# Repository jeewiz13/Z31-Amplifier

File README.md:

# Z31-Amplifier
New Amplifier that fits into stock Z31 Amplifier Housing
This isn't for the faint of heart.  This requires desoldering skills as the original header and DIN socket are reused.
It could use a few tweaks with spacing of the amplifier chips. They are off a little left or right. The footprints could also use a few tweaks as well. Works as is though. 
I originally thought the amplifier chips wouldn't fit inbetween the original metal mounting clamps.  They do but I was going to make an adapter out of aluminum to have it sink to the case. This spacing is rather large.  This spacing should be resolved if another version were to be made.

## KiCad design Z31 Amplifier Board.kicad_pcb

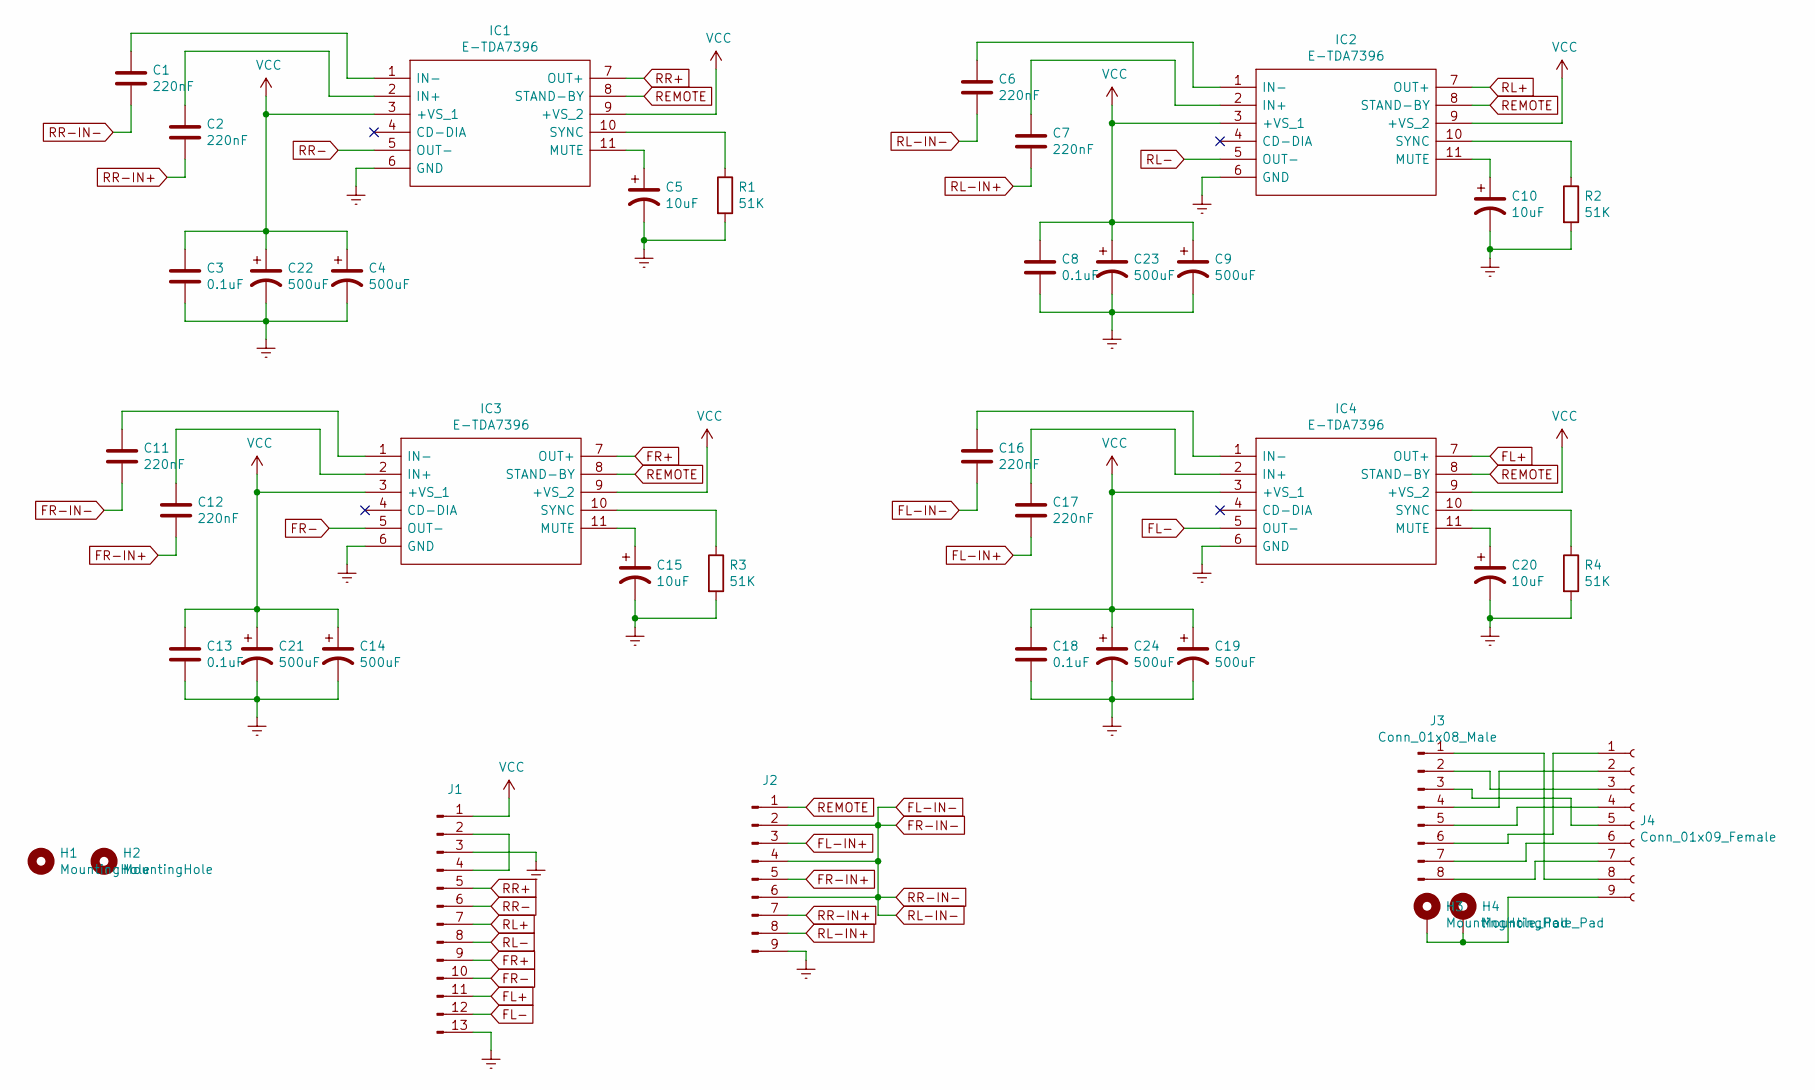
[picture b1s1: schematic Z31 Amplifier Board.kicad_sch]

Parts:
C1, C2, C6, C7, C11, C12, C16, C17: 220nF; C_Rect_L7.2mm_W2.5mm_P5.00mm_FKS2_FKP2_MKS2_MKP2
C3, C8, C13, C18: 0.1uF; C_Disc_D3.8mm_W2.6mm_P2.50mm
C4, C9, C14, C19, C21, C22, C23, C24: 500uF; CP_Radial_D10.0mm_P5.00mm
C5, C10, C15, C20: 10uF; CP_Radial_D5.0mm_P2.00mm
H1, H2: MountingHole; MountingHole_4.3mm_M4_ISO14580_Pad_TopBottom
H3, H4: MountingHole_Pad; MountingHole_2.5mm_Pad
IC1, IC2, IC3, IC4: E-TDA7396; TO170P500X1960X2210-11P; Mouser Part Number 511-E-TDA7396
J1: Conn_01x13_Male; Z31 Big Connector
J2: Conn_01x09_Male; Z31 Input Connector
J3: Conn_01x08_Male; 300ZX DIN Board Edge Connector
J4: Conn_01x09_Female; Din-8 Socket
R1, R2, R3, R4: 51K; R_Axial_DIN0309_L9.0mm_D3.2mm_P15.24mm_Horizontal

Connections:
Earth: C3.2, C4.2, C5.2, C8.2, C9.2, C10.2, C13.2, C14.2, C15.2, C18.2, C19.2, C20.2, C21.2, C22.2, C23.2, C24.2, IC1.6 (GND), IC2.6 (GND), IC3.6 (GND), IC4.6 (GND), J1.3, J1.13, J2.9, R1.2, R2.2, R3.2, R4.2
FL+: IC4.7 (OUT+), J1.11
FL-: IC4.5 (OUT-), J1.12
FL-IN+: C17.2, J2.3
FL-IN-: C1.2, C6.2, C11.2, C16.2, J2.2, J2.4, J2.6
FR+: IC3.7 (OUT+), J1.9
FR-: IC3.5 (OUT-), J1.10
FR-IN+: C12.2, J2.5
unnamed: C1.1, IC1.1 (IN-)
unnamed: C2.1, IC1.2 (IN+)
unnamed: C5.1, IC1.11 (MUTE)
unnamed: C6.1, IC2.1 (IN-)
unnamed: C7.1, IC2.2 (IN+)
unnamed: C10.1, IC2.11 (MUTE)
unnamed: C11.1, IC3.1 (IN-)
unnamed: C12.1, IC3.2 (IN+)
unnamed: C15.1, IC3.11 (MUTE)
unnamed: C16.1, IC4.1 (IN-)
unnamed: C17.1, IC4.2 (IN+)
unnamed: C20.1, IC4.11 (MUTE)
unnamed: H3.1, H4.1, J4.9
unnamed: IC1.10 (SYNC), R1.1
unnamed: IC2.10 (SYNC), R2.1
unnamed: IC3.10 (SYNC), R3.1
unnamed: IC4.10 (SYNC), R4.1
unnamed: J1.2, J1.4
unnamed: J3.1, J4.8
unnamed: J3.2, J4.3
unnamed: J3.3, J4.5
unnamed: J3.4, J4.2
unnamed: J3.5, J4.4
unnamed: J3.6, J4.1
unnamed: J3.7, J4.6
unnamed: J3.8, J4.7
REMOTE: IC1.8 (STAND-BY), IC2.8 (STAND-BY), IC3.8 (STAND-BY), IC4.8 (STAND-BY), J2.1
RL+: IC2.7 (OUT+), J1.7
RL-: IC2.5 (OUT-), J1.8
RL-IN+: C7.2, J2.8
RR+: IC1.7 (OUT+), J1.5
RR-: IC1.5 (OUT-), J1.6
RR-IN+: C2.2, J2.7
VCC: C3.1, C4.1, C8.1, C9.1, C13.1, C14.1, C18.1, C19.1, C21.1, C22.1, C23.1, C24.1, IC1.3 (+VS_1), IC1.9 (+VS_2), IC2.3 (+VS_1), IC2.9 (+VS_2), IC3.3 (+VS_1), IC3.9 (+VS_2), IC4.3 (+VS_1), IC4.9 (+VS_2), J1.1

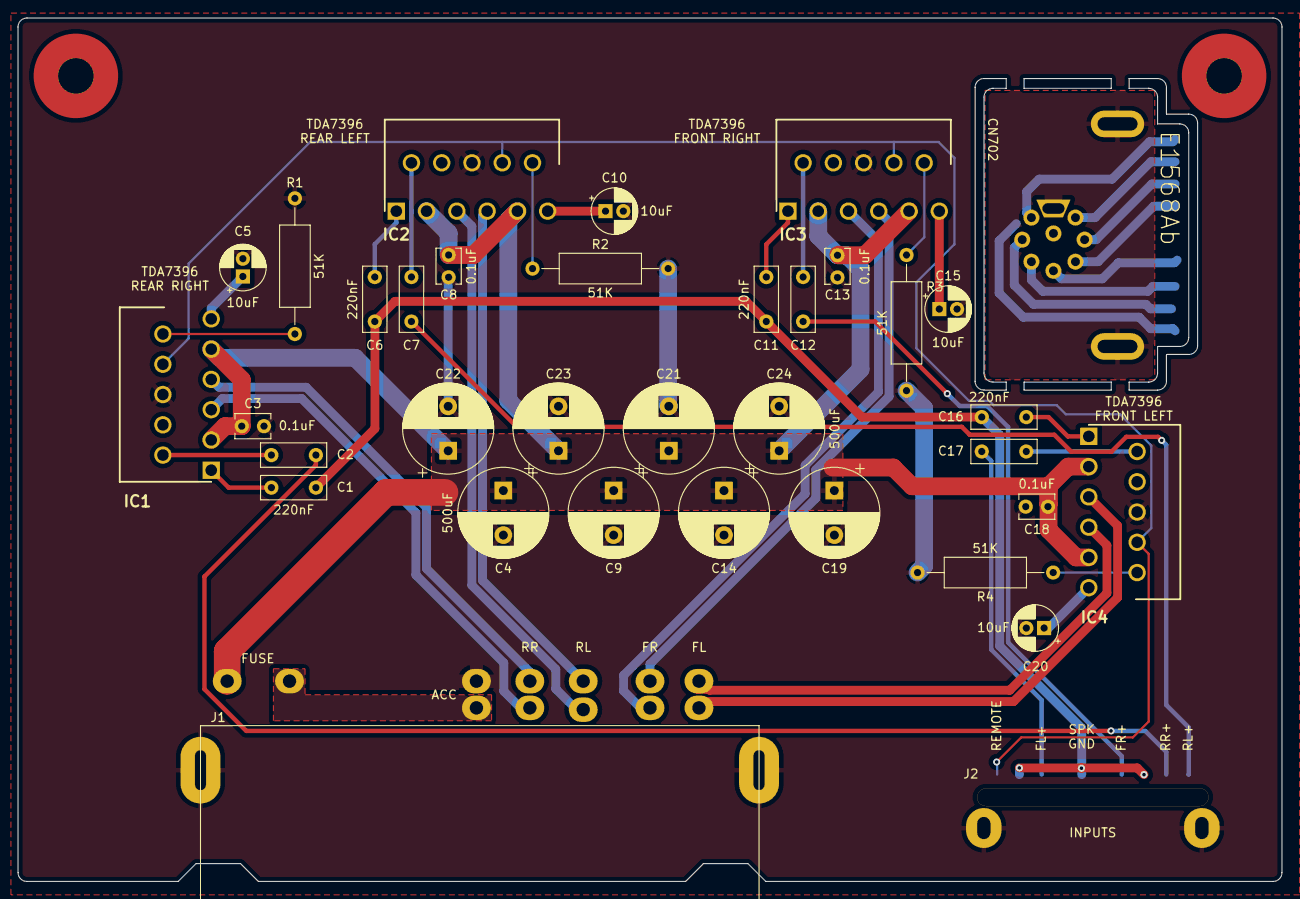
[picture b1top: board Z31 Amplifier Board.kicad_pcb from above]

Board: 2 copper layers, 142.0 x 97.0 mm, 40 parts (0 on the bottom side), 42 nets.

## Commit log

2022-01-23 Create footprint
2022-01-23 Create bom
2022-01-23 Create gerber
